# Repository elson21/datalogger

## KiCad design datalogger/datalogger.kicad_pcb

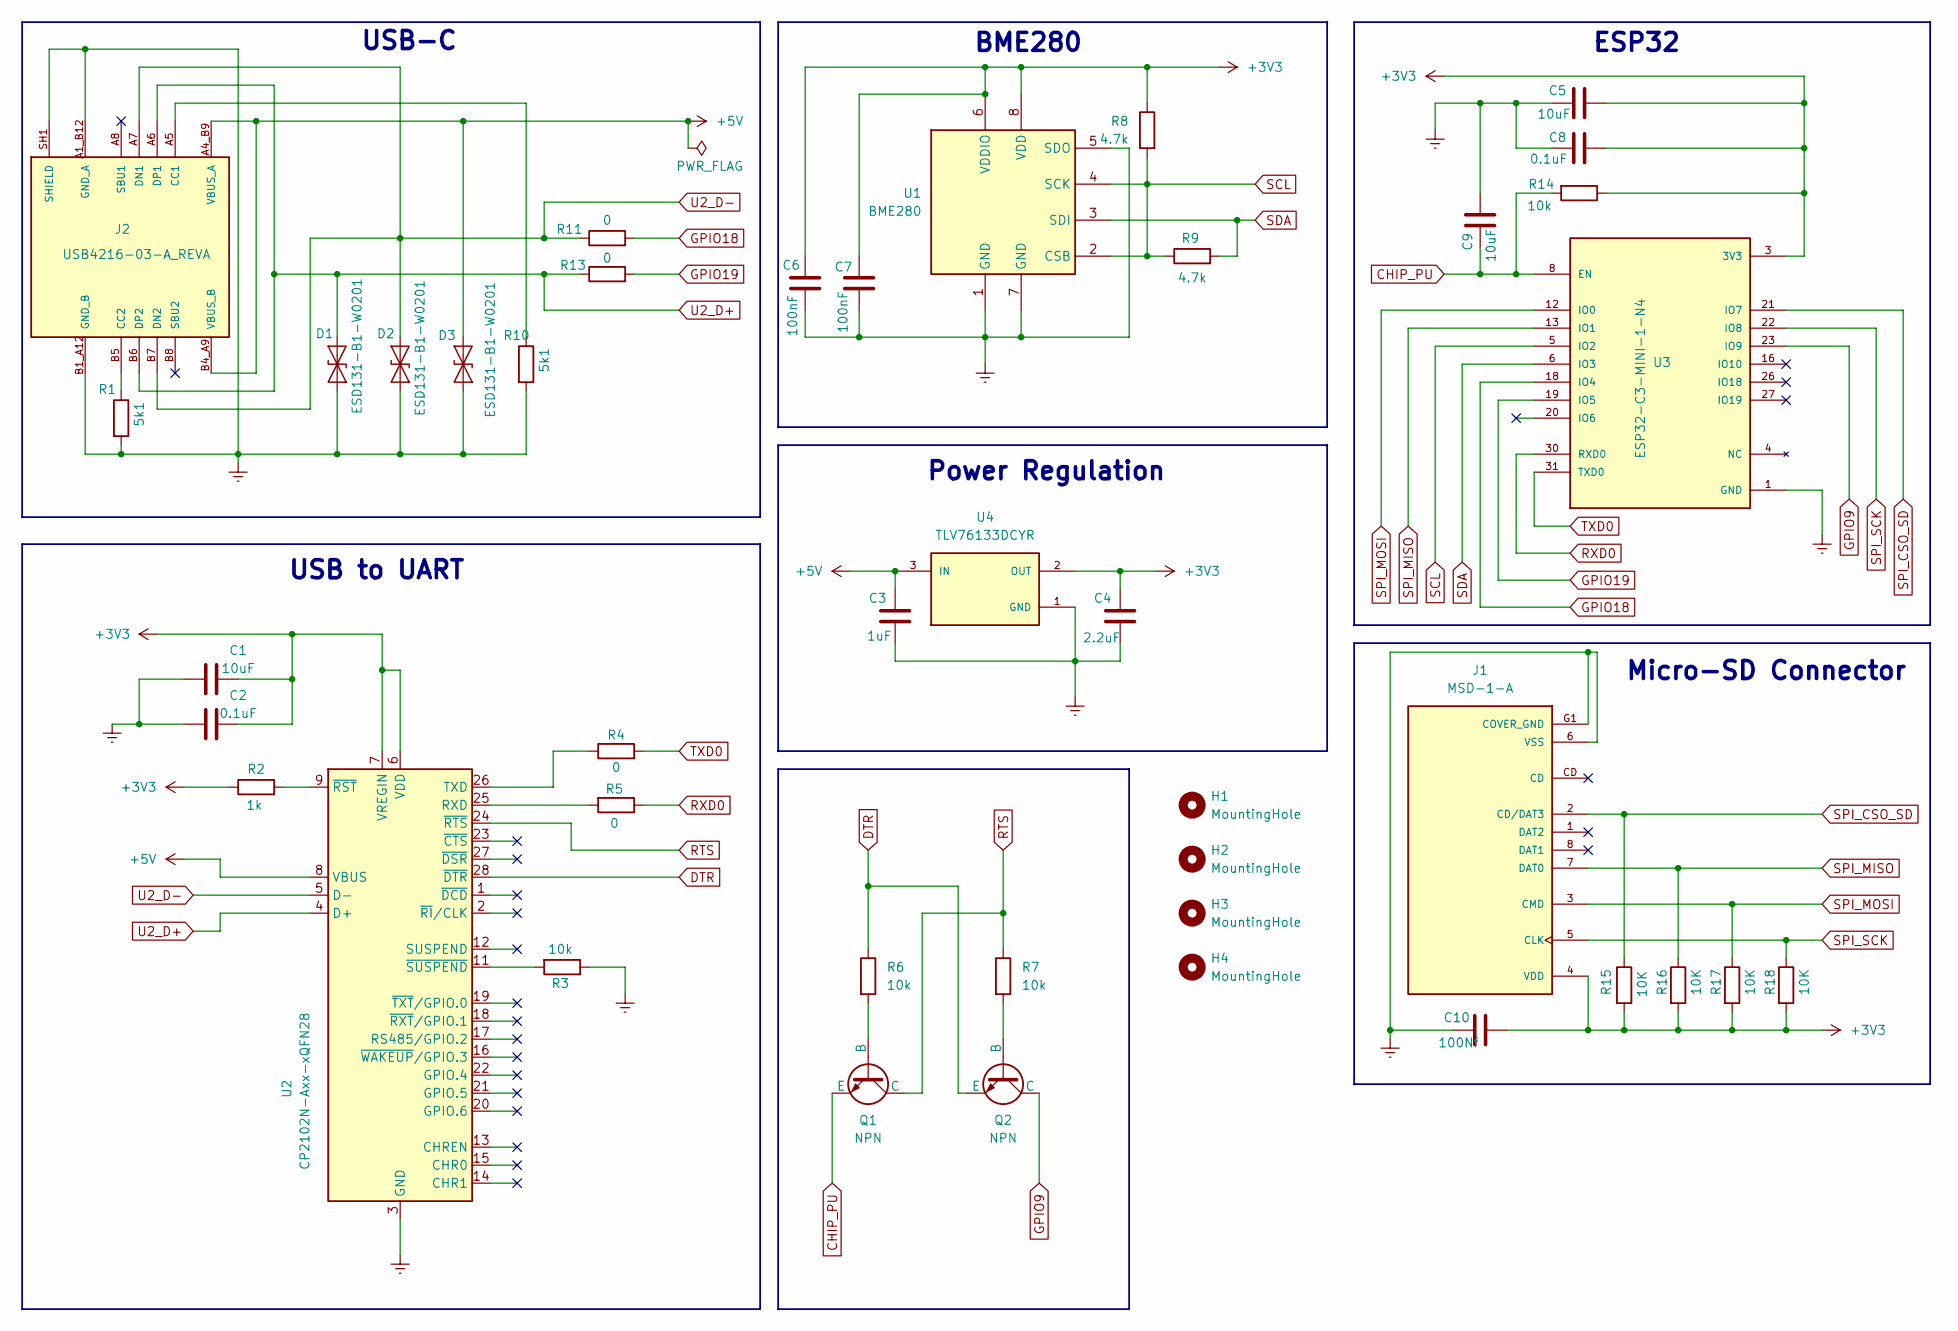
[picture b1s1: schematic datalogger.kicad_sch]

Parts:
C1, C5, C9: 10uF; C_0603_1608Metric
C2, C8: 0.1uF; C_0402_1005Metric
C3: 1uF; C_0402_1005Metric
C4: 2.2uF; C_0402_1005Metric
C6, C7: 100nF; C_0402_1005Metric
C10: 100Nf; C_0402_1005Metric
D1, D2, D3: ESD131-B1-W0201; Infineon_SG-WLL-2-3_0.58x0.28_P0.36mm
H1, H2, H3, H4: MountingHole; MountingHole_2.5mm_Pad_Via
J1: MSD-1-A; CUI_MSD-1-A; PARTREV 1.0
J2: USB4216-03-A_REVA; GCT_USB4216-03-A_REVA; PARTREV A
Q1, Q2: NPN; TRANS_BC847B
R1, R10: 5k1; R_0402_1005Metric
R2: 1k; R_0402_1005Metric
R3, R6, R7, R14: 10k; R_0402_1005Metric
R4, R5, R11, R13: 0; R_0402_1005Metric
R8, R9: 4.7k; R_0402_1005Metric
R15, R16, R17, R18: 10K; R_0402_1005Metric
U1: BME280; Bosch_LGA-8_2.5x2.5mm_P0.65mm_ClockwisePinNumbering
U2: CP2102N-Axx-xQFN28; QFN-28-1EP_5x5mm_P0.5mm_EP3.35x3.35mm
U3: ESP32-C3-MINI-1-N4; XCVR_ESP32-C3-MINI-1-N4; PARTREV v1.0
U4: TLV76133DCYR; VREG_TLV76133DCYR; PARTREV B

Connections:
+3V3: C1.2, C2.2, C4.1, C5.2, C6.1, C7.1, C8.2, C10.2, J1.4 (VDD), R2.1, R8.1, R14.1, R15.2, R16.2, R17.2, R18.2, U1.6 (VDDIO), U1.8 (VDD), U2.6 (VDD), U2.7 (VREGIN), U3.3 (3V3), U4.2 (OUT), U4.4 (OUT)
+5V: C3.1, D3.2 (A2), J2.A4_B9 (VBUS_A), J2.B4_A9 (VBUS_B), U2.8 (VBUS), U4.3 (IN)
CHIP_PU: C9.1, Q1.3 (E), R14.2, U3.8 (EN)
DTR: Q2.3 (E), R6.1, U2.28 (~DTR)
GNDREF: C1.1, C2.1, C3.2, C4.2, C5.1, C6.2, C7.2, C8.1, C9.2, C10.1, D1.1 (A1), D2.1 (A1), D3.1 (A1), J1.6 (VSS), J1.G1 (COVER_GND), J1.G2 (COVER_GND), J1.G3 (COVER_GND), J1.G4 (COVER_GND), J2.A1_B12 (GND_A), J2.B1_A12 (GND_B), J2.SH1 (SHIELD), J2.SH2 (SHIELD), J2.SH3 (SHIELD), J2.SH4 (SHIELD), R1.2, R3.1, R10.2, U1.1 (GND), U1.5 (SDO), U1.7 (GND), U2.3 (GND), U2.29 (GND), U3.1 (GND), U3.2 (GND), U3.11 (GND), U3.14 (GND), U3.36 (GND), U3.37 (GND), U3.38 (GND), U3.39 (GND), U3.40 (GND), U3.41 (GND), U3.42 (GND), U3.43 (GND), U3.44 (GND), U3.45 (GND), U3.46 (GND), U3.47 (GND), U3.48 (GND), U3.49_1 (GND), U3.49_2 (GND), U3.49_3 (GND), U3.49_4 (GND), U3.49_5 (GND), U3.49_6 (GND), U3.49_7 (GND), U3.49_8 (GND), U3.49_9 (GND), U3.50 (GND), U3.51 (GND), U3.52 (GND), U3.53 (GND), U4.1 (GND)
GPIO9: Q2.1 (C), U3.23 (IO9)
GPIO18: R11.2, U3.18 (IO4)
GPIO19: R13.2, U3.19 (IO5)
unnamed: J2.A5 (CC1), R10.1
unnamed: J2.B5 (CC2), R1.1
unnamed: Q1.2 (B), R6.2
unnamed: Q2.2 (B), R7.2
unnamed: R5.2, U2.25 (RXD)
unnamed: R4.1, U2.26 (TXD)
unnamed: R2.2, U2.9 (~RST)
unnamed: R3.2, U2.11 (~SUSPEND)
RTS: Q1.1 (C), R7.1, U2.24 (~RTS)
RXD0: R5.1, U3.30 (RXD0)
SCL: R8.2, R9.1, U1.2 (CSB), U1.4 (SCK), U3.5 (IO2)
SDA: R9.2, U1.3 (SDI), U3.6 (IO3)
SPI_CSO_SD: J1.2 (CD/DAT3), R15.1, U3.21 (IO7)
SPI_MISO: J1.7 (DAT0), R16.1, U3.13 (IO1)
SPI_MOSI: J1.3 (CMD), R17.1, U3.12 (IO0)
SPI_SCK: J1.5 (CLK), R18.1, U3.22 (IO8)
TXD0: R4.2, U3.31 (TXD0)
U2_D+: D1.2 (A2), J2.A6 (DP1), J2.B6 (DP2), R13.1, U2.4 (D+)
U2_D-: D2.2 (A2), J2.A7 (DN1), J2.B7 (DN2), R11.1, U2.5 (D-)

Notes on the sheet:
Micro-SD Connector
USB-C
ESP32
BME280
USB to UART
Power Regulation

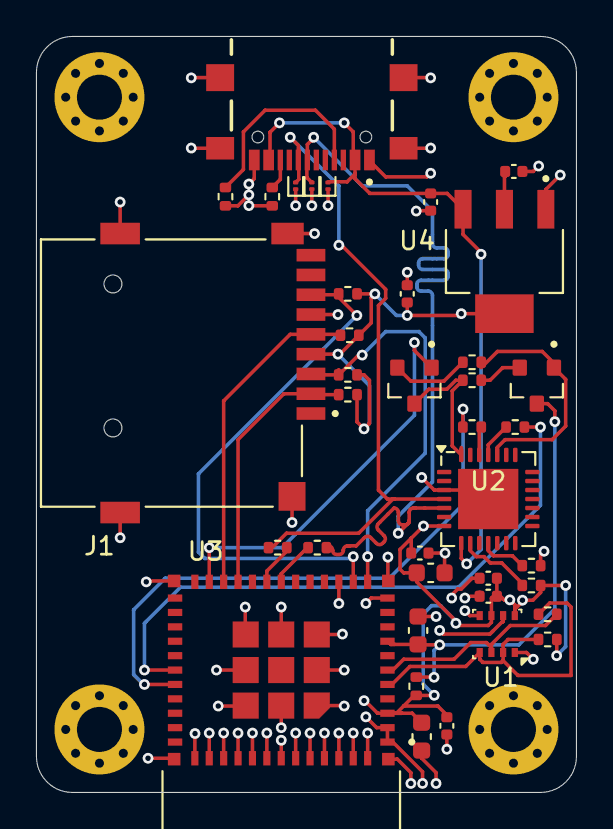
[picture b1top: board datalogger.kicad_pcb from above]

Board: 4 copper layers, 30.0 x 42.0 mm, 42 parts (0 on the bottom side), 27 nets.

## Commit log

2026-01-12 Change USB-C orientation
